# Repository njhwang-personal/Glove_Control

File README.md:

# Glove-Controlled Drone

## Overview
This project implements a wearable glove controller for drone control using a custom PCB, wireless communication, and a simulated drone environment.

## Repository Contents
- `glove_ctrl.py` – Webots controller code
- `glove_main.c` – STM32 firmware (STM32CubeIDE)
- `pi_receiver_final.c` – Raspberry Pi RF receiver and UDP bridge
- `Glove_32pin.kicad*` – KiCad schematic and PCB layout files for the glove controller

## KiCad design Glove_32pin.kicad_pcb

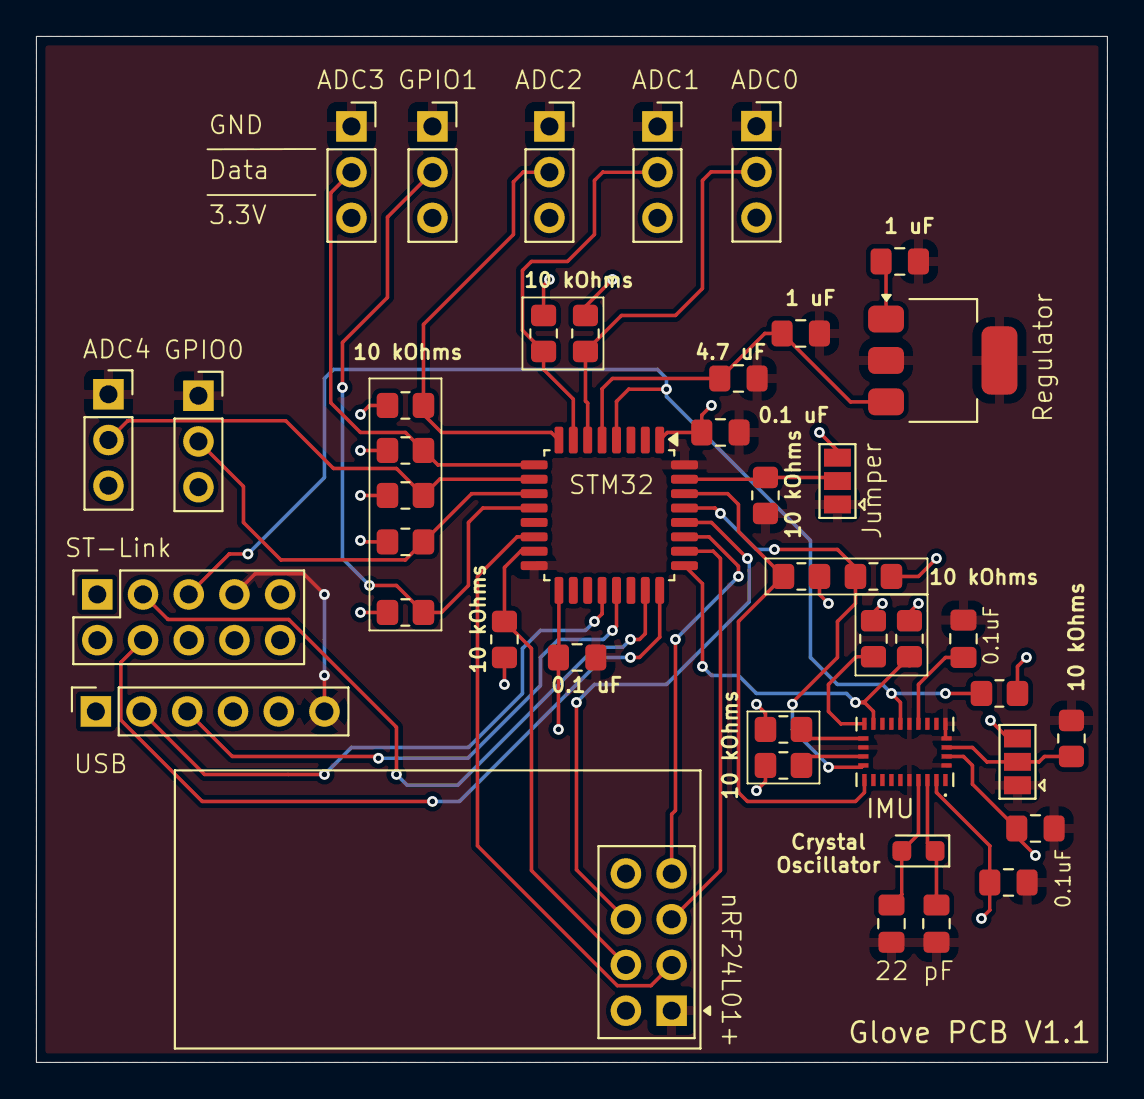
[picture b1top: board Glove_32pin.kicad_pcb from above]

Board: 2 copper layers, 59.5 x 57.0 mm, 43 parts (0 on the bottom side), 32 nets.

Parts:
C1, C2: 1 uF; C_0805_2012Metric_Pad1.18x1.45mm_HandSolder
C3, C4, C6, C7, C10: 0.1 uF; C_0805_2012Metric_Pad1.18x1.45mm_HandSolder
C5: 4.7 uF; C_0805_2012Metric_Pad1.18x1.45mm_HandSolder
C8, C9: 22 pF; C_0805_2012Metric_Pad1.18x1.45mm_HandSolder
J3, J4, J5, J6, J7, J8, J9: Conn_01x03_Pin; PinSocket_1x03_P2.54mm_Vertical
J10: ST-Link; PinSocket_2x05_P2.54mm_Vertical
J12: Conn_01x06_Socket; PinSocket_1x06_P2.54mm_Vertical
JP1, JP4: SolderJumper_3_Open; SolderJumper-3_P1.3mm_Open_Pad1.0x1.5mm
R1, R13: 10KOhms; R_0805_2012Metric_Pad1.20x1.40mm_HandSolder
R2, R3, R4, R12: 4.7 kOhms; R_0805_2012Metric_Pad1.20x1.40mm_HandSolder
R5, R6, R7, R8, R9, R10, R11: 22 kOhms; R_0805_2012Metric_Pad1.20x1.40mm_HandSolder
R14, R15, R16, R19: 10K; R_0805_2012Metric_Pad1.20x1.40mm_HandSolder
U1: STM32L031K6Tx; LQFP-32_7x7mm_P0.8mm
U2: TC1262-33; SOT-223-3_TabPin2
U3: BNO085; IC_BNO085
U5: NRF24L01_Breakout; nRF24L01_Breakout
X1: 32.768; Crystal_SMD_2012-2Pin_2.0x1.2mm_HandSoldering

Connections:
+3.3V: C3.2, C4.1, C7.1, C10.1, J3.3, J4.3, J5.3, J6.3, J7.3, J8.3, J9.3, J10.1, J10.6, JP1.3 (B), JP4.3 (B), R2.2, R3.2, R4.2, R5.1, R6.1, R7.1, R8.1, R9.1, R10.1, R11.1, R12.2, R14.2, R15.2, R16.1, R19.1, U1.1 (VDD), U1.17 (VDD), U3.3 (VDD), U3.28 (VDDIO), U5.2 (VCC)
+5V: C2.1, U2.1 (VI)
/ADC0: J3.2, R5.2, U1.6 (PA0)
/ADC1: J4.2, R6.2, U1.7 (PA1)
/ADC2: J5.2, R7.2, U1.8 (PA2)
/ADC3: J6.2, R8.2, U1.9 (PA3)
/ADC4: J7.2, R9.2, U1.10 (PA4)
/GPIO_0: J8.2, R10.2, U1.11 (PA5)
/GPIO_1: J9.2, R11.2, U1.12 (PA6)
/I2C_SCL: R3.1, U1.29 (PB6), U3.19 (H_SCL/SCK/RX)
/I2C_SDA: R2.1, U1.30 (PB7), U3.20 (H_SDA/H_MISO/TX)
/INT: R12.1, U1.25 (PA15), U3.14 (~H_INT)
/LPUART_Rx: J12.3, U1.21 (PA11)
/LPUART_Tx: J12.2, U1.20 (PA10)
/NRST: J10.5, R19.2, U1.4 (NRST), U3.11 (~RST)
/SPI_CE: U1.14 (PB0), U5.3 (CE)
/SPI_CSN: R4.1, U1.15 (PB1), U5.4 (~CSN)
/SPI_MISO: U1.27 (PB4), U5.7 (MISO)
/SPI_MOSI: U1.28 (PB5), U5.6 (MOSI)
/SPI_SCK: U1.26 (PB3), U5.5 (SCK)
/SWCLK: J10.4, U1.24 (PA14)
/SWDIO: J10.3, U1.23 (PA13)
/XIN: C8.1, U3.27 (XIN32), X1.1
/XOUT: C9.1, U3.26 (XOUT32/CLKSEL1), X1.2
GND: C1.2, C2.2, C3.1, C4.2, C5.2, C6.2, C7.2, C8.2, C9.2, C10.2, J3.1, J4.1, J5.1, J6.1, J7.1, J8.1, J9.1, J10.7, J12.6, JP1.1 (A), JP4.1 (A), R1.2, R13.2, U1.16 (VSS), U1.32 (VSS), U2.2 (GND), U3.2 (GND), U3.5 (PS1), U3.6 (PS0/WAKE), U3.10 (CLKSEL0), U3.17 (SA0/H_MOSI), U3.25 (GNDIO), U5.1 (GND)
unnamed: JP1.2 (C), R1.1, U1.31 (BOOT0)
unnamed: JP4.2 (C), R13.1, U3.4 (~BOOT)
unnamed: C1.1, C5.1, U1.5 (VDDA), U2.3 (VO)
unnamed: C6.1, U3.9 (CAP)
unnamed: R14.1, U3.15 (ENV_SCL)
unnamed: R15.1, U3.16 (ENV_SDA)
unnamed: R16.2, U3.18 (~H_CS)

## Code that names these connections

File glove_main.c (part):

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  /*Configure GPIO pin Output Level */
  HAL_GPIO_WritePin(GPIOB, GPIO_PIN_0|GPIO_PIN_1, GPIO_PIN_RESET);

  /*Configure GPIO pins : PA5 PA6 PA15 */
  GPIO_InitStruct.Pin = GPIO_PIN_5|GPIO_PIN_6|GPIO_PIN_15;
  GPIO_InitStruct.Mode = GPIO_MODE_INPUT;
  GPIO_InitStruct.Pull = GPIO_NOPULL;
  HAL_GPIO_Init(GPIOA, &GPIO_InitStruct);

  /*Configure GPIO pins : PB0 PB1 */
  GPIO_InitStruct.Pin = GPIO_PIN_0|GPIO_PIN_1;
  GPIO_InitStruct.Mode = GPIO_MODE_OUTPUT_PP;
  GPIO_InitStruct.Pull = GPIO_NOPULL;
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
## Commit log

2025-12-17 3D print model
2025-12-17 Final Design Photos

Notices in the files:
glove_main.c:
Copyright (c) 2025 STMicroelectronics.
All rights reserved.
This software is licensed under terms that can be found in the LICENSE file
